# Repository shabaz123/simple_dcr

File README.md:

# Simple Direct Conversion Receiver for 40m (7 MHz) Band

This project is based on https://hackaday.io/project/190327/files

The main difference is that the project has been converted to a printed circuit board layout.

# Ordering

To order a PCB, [Click here for the PCB Gerber Zip File](https://github.com/shabaz123/simple_dcr/raw/main/gerber-export-dcr-pcbver-rev1_0.zip) and then upload it to any PCB manufacturer. The board is 2-layer, 160 x 100 mm in size.

The 3D-print file for constructing the variable inductor is available from the Hackaday website [(direct link to the file)](https://cdn.hackaday.io/files/1903278142950368/PTO%20Former%20-%20print%20at%20110%20pct.stl).

The parts list is in a table further below.

# Circuit Diagram

[Click here for the PDF version](https://github.com/shabaz123/simple_dcr/raw/main/dcr-schematic-rev1_0.pdf)

# Board Layout

## Board Underside

# Toroid Detail

## TR1, TR2

T50-6 Iron Powder

Pins 1-2: 26 Turns

Pins 6-4: 5 Turns

## TR3, TR4:

FT50-43 Ferrite

10 Turns Trifilar

Three Windings: Red, Green, Blue

Pin 4: Red end A

Pin 6: Red end B

Pin 1: Green end A

Pin 3: Blue end B

Pin 2: Remaining ends (Green end B, Blue end A)

# Parts List

**Reference**|**Value**|**Qty**|**Description**
-----|-----|-----|-----
C1,C2|2 x 330pF in Parallel|4|NP0 Ceramic Capacitors (660pF combined)
C3|130p|1|NP0 Ceramic Capacitor
C4,C5,C6,C7|0.1u|4|Ceramic Capacitor
C8,C14|10u|2|Electrolytic Capacitor
C9,C11,C13|470u|3|Electrolytic Capacitor
C10,C12,C15|47u|2|Electrolytic Capacitor
C16|0.47u|1|Ceramic Capacitor
C17|33u|1|Electrolytic Capacitor
C18,C19|2 x 330pF in Series|4|NP0 Ceramic Capacitors (165pF combined)
C20|10p|1|NP0 Ceramic Capacitor
C21,C22,C23|Optional|3|40pF Trimmer Capacitors
D1|BZX55C8V2|1|Zener Diode 8.2V
D2,D3,D4,D5|1N5819|4|Schottky Diode
J1|Antenna|1|3.5mm or 3.8mm 2-way Screw Terminal Block
J2|Speaker|1|8 ohm Speaker
J3|9V Battery|1|PP3 Battery Connector
L1|Variable Inductor|1|19 Turns on 3D-printed Former
L2|10u|1|Axial Inductor
L11|100uH|1|Axial Inductor
Q1,Q3,Q4,Q5|2N3904|4|NPN Transistor
Q2|J310|1|N-ch JFET
R1,R2|10k|2|Resistor
R3|3.3k|1|Resistor
R4,R6,R14|100R|3|Resistor
R5|100k|1|Resistor
R7|47R|1|Resistor
R8,R12,R16|15k|3|Resistor
R9,R13,R17|4.7k|3|Resistor
R10,R18|1k|2|Resistor
R11,R19|470R|2|Resistor
R20|220R|1|Resistor
SW1|SPDT|1|Right-Angle SPDT Toggle Switch
TR1,TR2|T50-6|2|Toroid Iron Powder Type 6
TR3,TR4|FT50-43|2|Toroid Ferrite Type 43
TR5|Transformer 1k/8R|1|Audio Transformer 1kohm:8ohm
VR1|1k|1|Potentiometer Log Audio (Type A)
n/a|Former|1|3D-printed Coil Former for Inductor
n/a|M6 Bolt BRASS|1|M6 75 or 80 mm Screw MUST be SOLID BRASS
n/a|M6 Nut|1|M6 Nut Ideally Brass
n/a|Enamelled Wire|1|Approx 24-26 AWG Enamelled Wire

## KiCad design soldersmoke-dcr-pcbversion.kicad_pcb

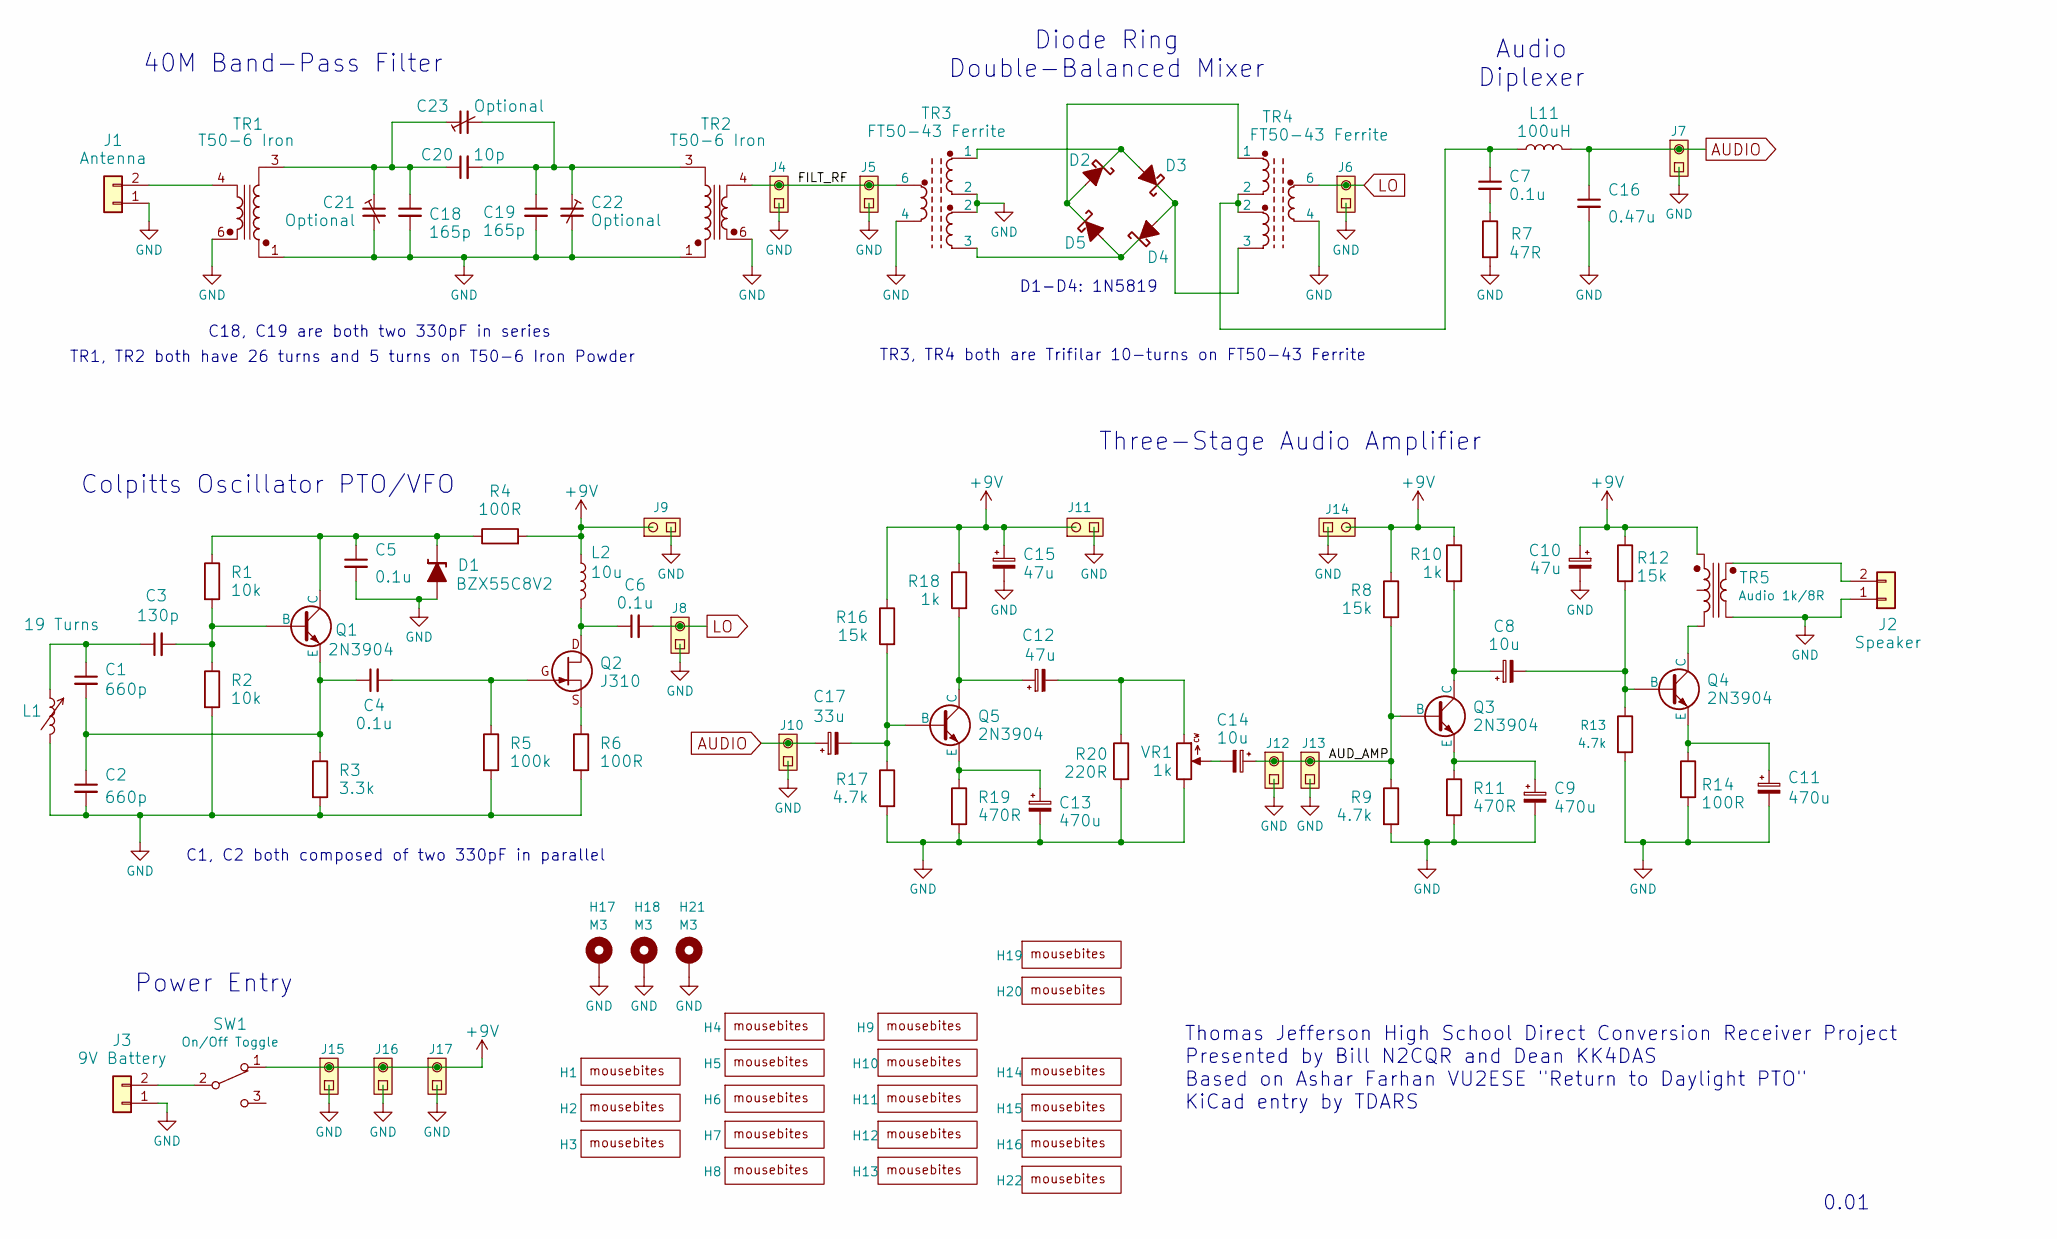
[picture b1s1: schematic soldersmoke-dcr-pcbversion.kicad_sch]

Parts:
C1, C2: 660p; C_Disc_Parallel_plus_1206_SMD_D3.0mm_W1.6mm_P5.0
C3: 130p; C_Disc_D3.0mm_W1.6mm_P5.0
C4, C5, C6, C7: 0.1u; C_Disc_D3.0mm_W1.6mm_P5.0
C8, C14: 10u; CP_Radial_D5.0mm_P2.50mm
C9, C11, C13: 470u; CP_Radial_D8mm_P3.5mm
C10, C15: 47u; CP_Radial_D6.3mm_P2.50mm
C12: 47u; CP_Radial_D5.0mm_P2.50mm
C16: 0.47u; C_Disc_D3.0mm_W1.6mm_P5.0
C17: 33u; CP_Radial_D5.0mm_P2.50mm
C18, C19: 165p; C_Disc_Series_plus_1206_SMD_D3.0mm_W1.6mm_P5.0
C20: 10p; C_Disc_D3.0mm_W1.6mm_P5.0
C21, C22, C23: Optional; C_Trim_Multisized
D1: BZX55C8V2; D_DO-35_SOD27_P7.62mm_Horizontal
D2, D3, D4, D5: 1N5819; D_DO-41_SOD81_P10.16mm_Horizontal_soldersmoke
H1, H2, H4, H5, H8, H10, H12, H13, H16, H20: mousebites-imperial-5-trackgap
H3, H6, H7, H9, H11, H14, H15, H19, H22: mousebites-imperial-5
H17, H18, H21: M3; MountingHole_3.2mm_M3_Pad
J1: Antenna; TerminalBlock_2way-3.5-3.81mm
J2: Speaker; TerminalBlock_2way-3.5-3.81mm
J3: 9V Battery; TerminalBlock_2way-3.5-3.81mm
J4, J5, J6, J7, J8, J9, J10, J11, J12, J13, J14, J15, J16, J17: PinHeader_1x02_P2.54mm_Vertical
L1: 19 Turns; variable-inductor-soldersmoke
L2: 10u; L_Axial_L9.5mm_D4.0mm_P12.70mm_Horizontal_Fastron_SMCC
L11: 100uH; L_Axial_L9.5mm_D4.0mm_P12.70mm_Horizontal_Fastron_SMCC
Q1, Q3, Q4, Q5: 2N3904; TO-92-soldersmoke
Q2: J310; TO-92-JFET-soldersmoke
R1, R2: 10k; R_Axial_DIN0207_L6.3mm_D2.5mm_P10.16mm_Horizontal
R3: 3.3k; R_Axial_DIN0207_L6.3mm_D2.5mm_P10.16mm_Horizontal
R4, R6, R14: 100R; R_Axial_DIN0207_L6.3mm_D2.5mm_P10.16mm_Horizontal
R5: 100k; R_Axial_DIN0207_L6.3mm_D2.5mm_P10.16mm_Horizontal
R7: 47R; R_Axial_DIN0207_L6.3mm_D2.5mm_P10.16mm_Horizontal
R8, R12, R16: 15k; R_Axial_DIN0207_L6.3mm_D2.5mm_P10.16mm_Horizontal
R9, R13, R17: 4.7k; R_Axial_DIN0207_L6.3mm_D2.5mm_P10.16mm_Horizontal
R10, R18: 1k; R_Axial_DIN0207_L6.3mm_D2.5mm_P10.16mm_Horizontal
R11, R19: 470R; R_Axial_DIN0207_L6.3mm_D2.5mm_P10.16mm_Horizontal
R20: 220R; R_Axial_DIN0207_L6.3mm_D2.5mm_P10.16mm_Horizontal
SW1: On/Off Toggle; SPDT-RA
TR1, TR2: T50-6 Iron; soldersmoke-toroid-ferrite-12.7
TR3, TR4: FT50-43 Ferrite; soldersmoke-toroid-CT-12.7
TR5: Audio 1k/8R; soldersmoke-audio-transformer
VR1: 1k; Potentiometer_soldersmoke

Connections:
+9V: C10.1, C15.1, J9.2, J11.2, J14.2, J15.2, J16.2, J17.2, L2.1, R4.2, R8.1, R10.1, R12.1, R16.1, R18.1, SW1.1 (A), TR5.1
/AUD_AMP: C14.1, J12.2, J13.2, Q3.2 (B), R8.2, R9.1
/FILT_RF: J4.2, J5.2, TR2.4, TR3.6
AUDIO: C16.1, C17.1, J7.2, J10.2, L11.2
GND: C2.2, C5.2, C9.2, C10.2, C11.2, C13.2, C15.2, C16.2, C18.2, C19.2, C21.1, C22.1, D1.2 (A), H17.1, H18.1, H21.1, J1.1, J2.1, J3.1, J4.1, J5.1, J6.1, J7.1, J8.1, J9.1, J10.1, J11.1, J12.1, J13.1, J14.1, J15.1, J16.1, J17.1, L1.1, R2.2, R3.2, R5.2, R6.2, R7.2, R9.2, R11.2, R13.2, R14.2, R17.2, R19.2, R20.2, TR1.1, TR1.6, TR2.1, TR2.6, TR3.2, TR3.4, TR4.4, TR5.6, VR1.1
LO: C6.2, J6.2, J8.2, TR4.6
unnamed: C1.1, C3.1, L1.2
unnamed: C7.1, L11.1, TR4.2
unnamed: C7.2, R7.1
unnamed: C12.2, R20.1, VR1.3
unnamed: C14.2, VR1.2
unnamed: C18.1, C20.1, C21.2, C23.2, TR1.3
unnamed: C19.1, C20.2, C22.2, C23.1, TR2.3
unnamed: C5.1, D1.1 (K), Q1.3 (C), R1.1, R4.1
unnamed: D2.2 (A), D5.1 (K), TR4.1
unnamed: D2.1 (K), D3.2 (A), TR3.1
unnamed: D3.1 (K), D4.2 (A), TR4.3
unnamed: D4.1 (K), D5.2 (A), TR3.3
unnamed: J1.2, TR1.4
unnamed: J2.2, TR5.4
unnamed: J3.2, SW1.2 (B)
unnamed: C3.2, Q1.2 (B), R1.2, R2.1
unnamed: C1.2, C2.1, C4.1, Q1.1 (E), R3.1
unnamed: C6.1, L2.2, Q2.1 (D)
unnamed: C4.2, Q2.3 (G), R5.1
unnamed: Q2.2 (S), R6.1
unnamed: C8.1, Q3.3 (C), R10.2
unnamed: C9.1, Q3.1 (E), R11.1
unnamed: C8.2, Q4.2 (B), R12.2, R13.1
unnamed: Q4.3 (C), TR5.3
unnamed: C11.1, Q4.1 (E), R14.1
unnamed: C17.2, Q5.2 (B), R16.2, R17.1
unnamed: C12.1, Q5.3 (C), R18.2
unnamed: C13.1, Q5.1 (E), R19.1

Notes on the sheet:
Audio Diplexer
Thomas Jefferson High School Direct Conversion Receiver Project Presented by Bill N2CQR and Dean KK4DAS Based on Ashar Farhan VU2ESE "Return to Daylight PTO" KiCad entry by TDARS
Colpitts Oscillator PTO/VFO
Three-Stage Audio Amplifier
Power Entry
C1, C2 both composed of two 330pF in parallel
Diode Ring Double-Balanced Mixer
40M Band-Pass Filter
C18, C19 are both two 330pF in series
TR3, TR4 both are Trifilar 10-turns on FT50-43 Ferrite
TR1, TR2 both have 26 turns and 5 turns on T50-6 Iron Powder
0.01
D1-D4: 1N5819

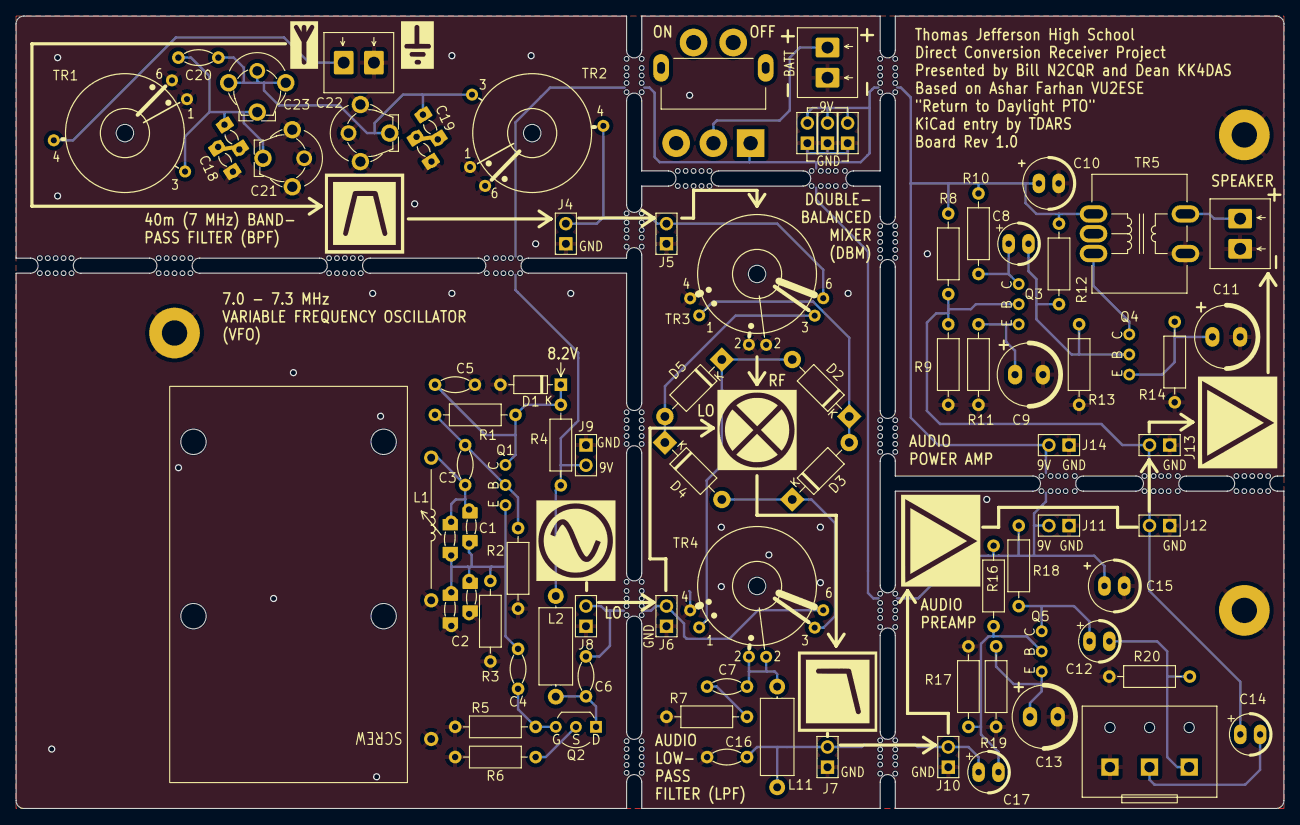
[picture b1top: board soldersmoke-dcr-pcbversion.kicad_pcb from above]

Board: 2 copper layers, 160.0 x 100.0 mm, 101 parts (0 on the bottom side), 34 nets.
